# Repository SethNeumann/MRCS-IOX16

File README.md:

# REPO NAME: MRCS-IOX16

## License: Creative Commons Attribution-NonCommercial-ShareAlike

The IOX16 provides an 16 additonal lines of i/o for the cpNode using the MCP23017 chip.
IOX16 lines are configurable in as input or output in 8 bit (1 byte) increments.
Up to 128 lines of i/o may be added to a cpNode in any combination of IOX16s and IOX32s for a total of 144 lines of i/o.
Input and output voltages are limited to 5V.
Each output may sink up to 25 mA subject to a device limit of 160mA, if all lines are used as output use 10mA as a design limit.
Since the vast majority of outputs in a model railroad signaling system are used for driving LEDS, 10mA should be adequate.
If you need to work with higher voltages or currents, use the CSNK adapter in conjunction with the IOX16.
Pads for inserting limiting resistors are provided for each line.
Output pads are spaced at 0.100" to allow you maximum flexibility in configuring outputs.

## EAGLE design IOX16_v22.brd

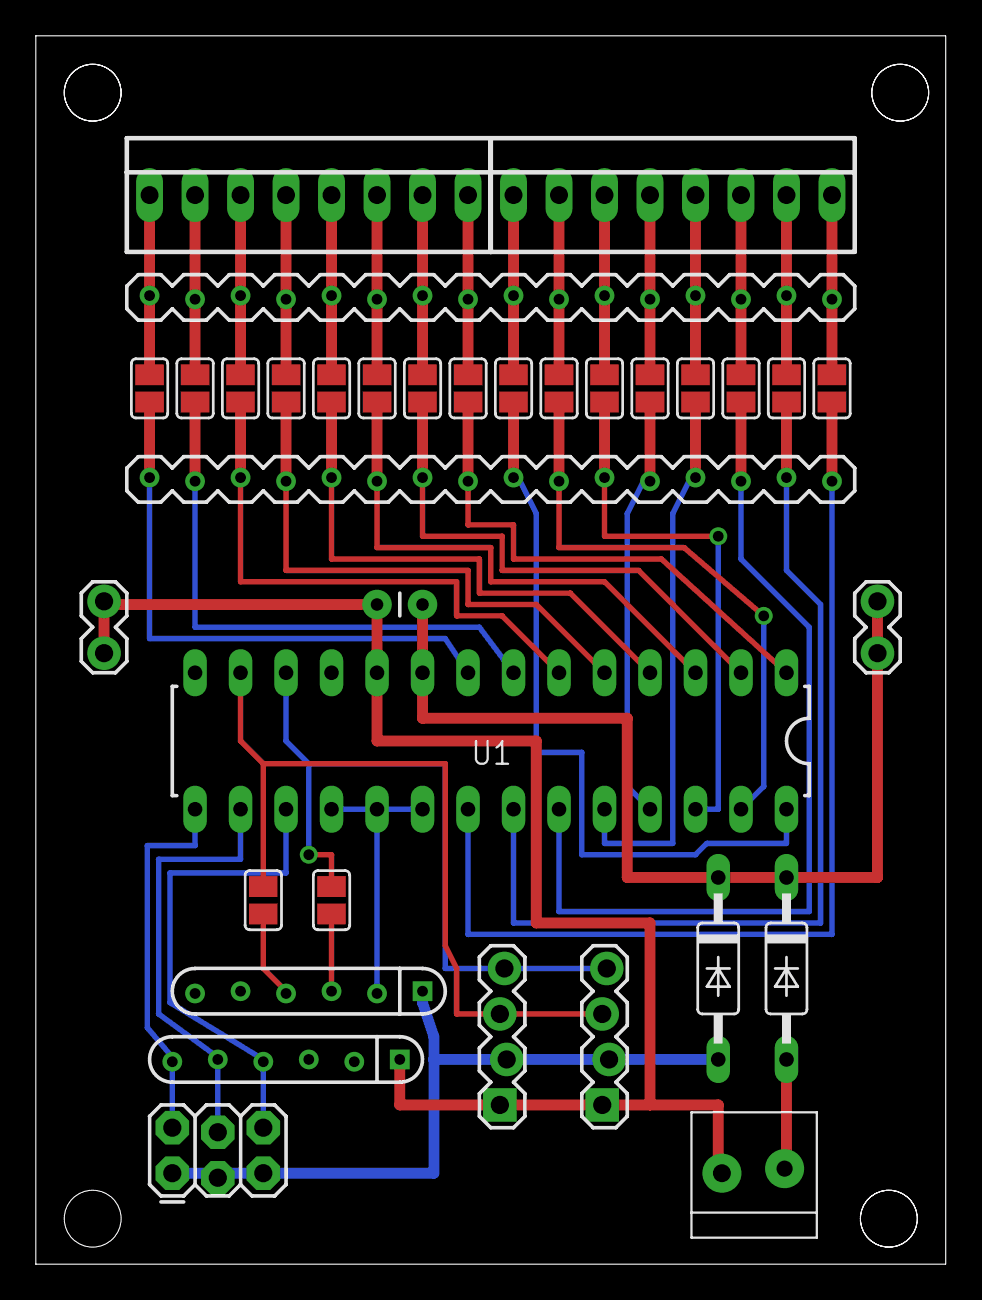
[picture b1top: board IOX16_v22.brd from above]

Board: 2 copper layers, 50.8 x 68.6 mm, 43 parts (0 on the bottom side), 3 nets.

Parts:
5V: 1X02_LOCK
ADDR: 2X3_LOCK
C1: .01uf; CAP-PTH-SMALL
COM: 1X02_LOCK
D1: D1; C2992
D2: D2; C2992
E$1, E$3: 1X16_MACHINE-PIN-HEADER_LOCK.004
E$2, E$4: 1X04_LOCK
E$6, E$7, E$8, E$10, E$12, E$13, E$14: DRILL_0.1250
E$9: MRCSLOGOTOP
E$11: CA-PROP65WARNING
E$15: 3.5MMTERM
I2CT1, I2CT2: 2P-SMD-2X3.3
PORTA: 22-23-2081
PORTB: 22-23-2081
RP1, RP2: RPACK-SIP-PTH-5
SJ1, SJ2, SJ3, SJ4, SJ5, SJ6, SJ7, SJ8, SJ9, SJ10, SJ11, SJ12, SJ13, SJ14, SJ15, SJ16: 2P-SMD-2X3.3
U1: MCP23017; DIL28-3

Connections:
S$7: U1.18, U1.19, U1.20
S$18: ADDR.2, U1.15
S$52: C1.1, U1.9

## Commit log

2024-01-11 Update DESCRIPTION
2024-01-11 Update INFO
2024-01-11 move existing files into Github
2024-01-11 Delete IOX16_v22_array.scr
    this is just a work file which is recreated when you run the panelizer
2024-01-11 Delete cpNode_IOX16_BOM_20180708 v2.2.xlsx
    removed old BOM, new one coming
2024-01-11 Create Build BOM.pdf
    Bill of Materials

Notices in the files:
parts and their libraries:
SparkFun-Connectors: Licensing: CC v3.0 Share-Alike You are welcome to use this library for commercial purposes.
